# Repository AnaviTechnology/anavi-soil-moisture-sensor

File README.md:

# ANAVI (Resistive) Soil Moisture Sensor

This is an open source hardware **resistive** soil moisture sensor.

Resistive soil moisture sensors have a lot of disadvantages and they are vulnerable to corrosion. **It is higly recommended to use capacitive soil moisture sensor instead!**

# Story

This resistive soil moisture sensor was designed with the first prototype of [ANAVI Gardening uHAT](https://github.com/AnaviTechnology/anavi-gardening) in 2017. After that, the project was put on hold for several years. In 2021 we revived [ANAVI Gardening uHAT](https://github.com/AnaviTechnology/anavi-gardening) using Microchip MCP3002 analog-to-digital converter (ADC) and 3rd party low-cost capacitive soil-moisture sensors made of corrosion-resistant materials.

# License

The project is released under the [Creative Commons Attribution-ShareAlike 4.0 International (CC BY-SA 4.0)](https://creativecommons.org/licenses/by-sa/4.0/).

Note: This is a human-readable summary of (and not a substitute for) the [license](https://creativecommons.org/licenses/by-sa/4.0/legalcode).

You are free to:

Share — copy and redistribute the material in any medium or format Adapt — remix, transform, and build upon the material for any purpose, even commercially. The licensor cannot revoke these freedoms as long as you follow the license terms. Under the following terms:

Attribution — You must give appropriate credit, provide a link to the license, and indicate if changes were made. You may do so in any reasonable manner, but not in any way that suggests the licensor endorses you or your use. ShareAlike — If you remix, transform, or build upon the material, you must distribute your contributions under the same license as the original. No additional restrictions — You may not apply legal terms or technological measures that legally restrict others from doing anything the license permits. Notices:

You do not have to comply with the license for elements of the material in the public domain or where your use is permitted by an applicable exception or limitation. No warranties are given. The license may not give you all of the permissions necessary for your intended use. For example, other rights such as publicity, privacy, or moral rights may limit how you use the material.

You will have to provide a link to the original creator of the project http://www.anavi.technology on any documentation or website.

Credit can be attributed through a link to the creator website: http://www.anavi.technology

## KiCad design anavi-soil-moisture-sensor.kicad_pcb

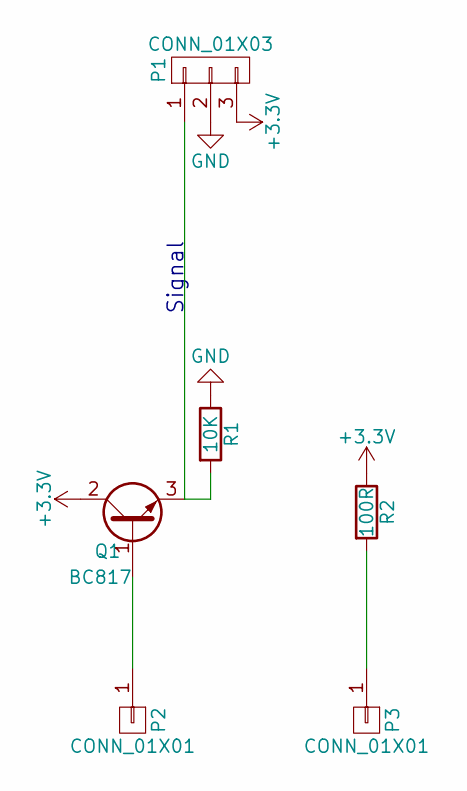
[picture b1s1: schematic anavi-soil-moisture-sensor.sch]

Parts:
P1: CONN_01X03; Pin_Header_Angled_1x03
P2, P3: CONN_01X01; SolderWirePad_single_0-8mmDrill
Q1: BC817; SOT-23
R1: 10K; R_0603_HandSoldering
R2: 100R; R_0603_HandSoldering

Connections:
+3V3: P1.3, Q1.2 (C), R2.1
GND: P1.2, R1.1
unnamed: P1.1, Q1.3 (E), R1.2
unnamed: P2.1, Q1.1 (B)
unnamed: P3.1, R2.2

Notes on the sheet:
Signal

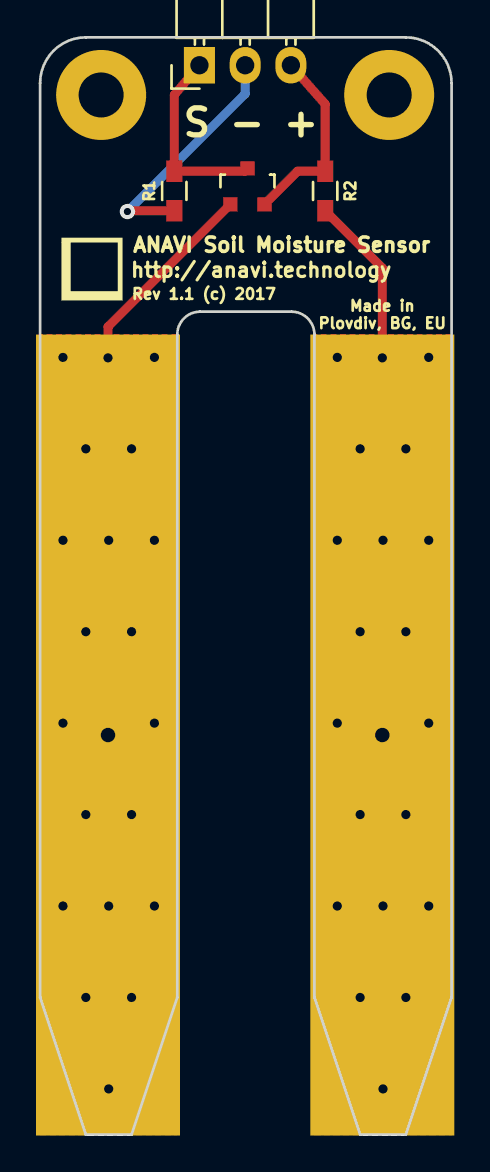
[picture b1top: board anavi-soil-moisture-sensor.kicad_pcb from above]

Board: 2 copper layers, 22.9 x 61.0 mm, 6 parts (0 on the bottom side), 5 nets.

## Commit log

2017-04-08 anavi-soil-moisture-sensor: Initial commit
2017-04-08 anavi-soil-moisture-sensor.kicad_pcb: fix rods
2017-04-09 anavi-soil-moisture-sensor.kicad_pcb: update zones
2017-04-10 anavi-soil-moisture-sensor.kicad_pcb: Adjust text
2017-04-13 anavi-soil-moisture-sensor.kicad_pcb: Fix pads
2017-04-13 anavi-soil-moisture-sensor.kicad_pcb: Add vias
2017-04-18 anavi-soil-moisture-sensor.kicad_pcb: Revision 1.1
2017-06-29 anavi-soil-moisture-sensor: Assembly guidelines
    Add labels for assembly guidelines of SMT components.
2021-10-30 README.md: Update details
    Add details about the project and ANAVI Gardening uHAT.

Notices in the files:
anavi-soil-moisture-sensor.kicad_pcb:
Rev 1.1 (c) 2017
